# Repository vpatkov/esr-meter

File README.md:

# ESR meter

Yet another ESR meter. More precisely, it measures the impedance at 100 kHz in
assumption it's pure resistive. So this meter is not for laboratory
measurements, but for finding bad electrolytic capacitors (a typical fault in
aged electronics).

- The test signal is 100 kHz 50 mVpp 10 Ω sine wave
- Rechargeable from Micro-USB at 300 mA (Li-Po/Li-ion)
- Auto power-off after 3 minutes of inactivity

## Usage

To switch the meter on or off, press the button.

On startup, the meter performs a self-test. Keep the terminals open. During the
test, the meter turns on all the segments on the display, then shows an error
if any. Errors are:

- `E.F.LO`: low fuel (battery voltage < 3.3 V);
- `E.rEF`: something wrong with voltage references or ADC;
- `E.Prb`: something wrong with the test signal (or the terminals aren't open).

When the test is passed, the meter shows the current battery level in percents
as `F <level>`.

During normal operation the meter continuously shows the measured ESR in Ω,
or `-OL-` if it's more than 99.99 Ω.

To compensate test leads (set zero), short the leads and long press the button.
You can't compensate more than 2 Ω — find a better leads or connect capacitors
directly to the binding post. Note that inductance of wires matters at 100 kHz.
If the meter refuse to compensate, it shows `SHIt` (stands for "your leads are
shit").

## License

Unless otherwise noted, this work is licensed under Creative Commons Zero 1.0.

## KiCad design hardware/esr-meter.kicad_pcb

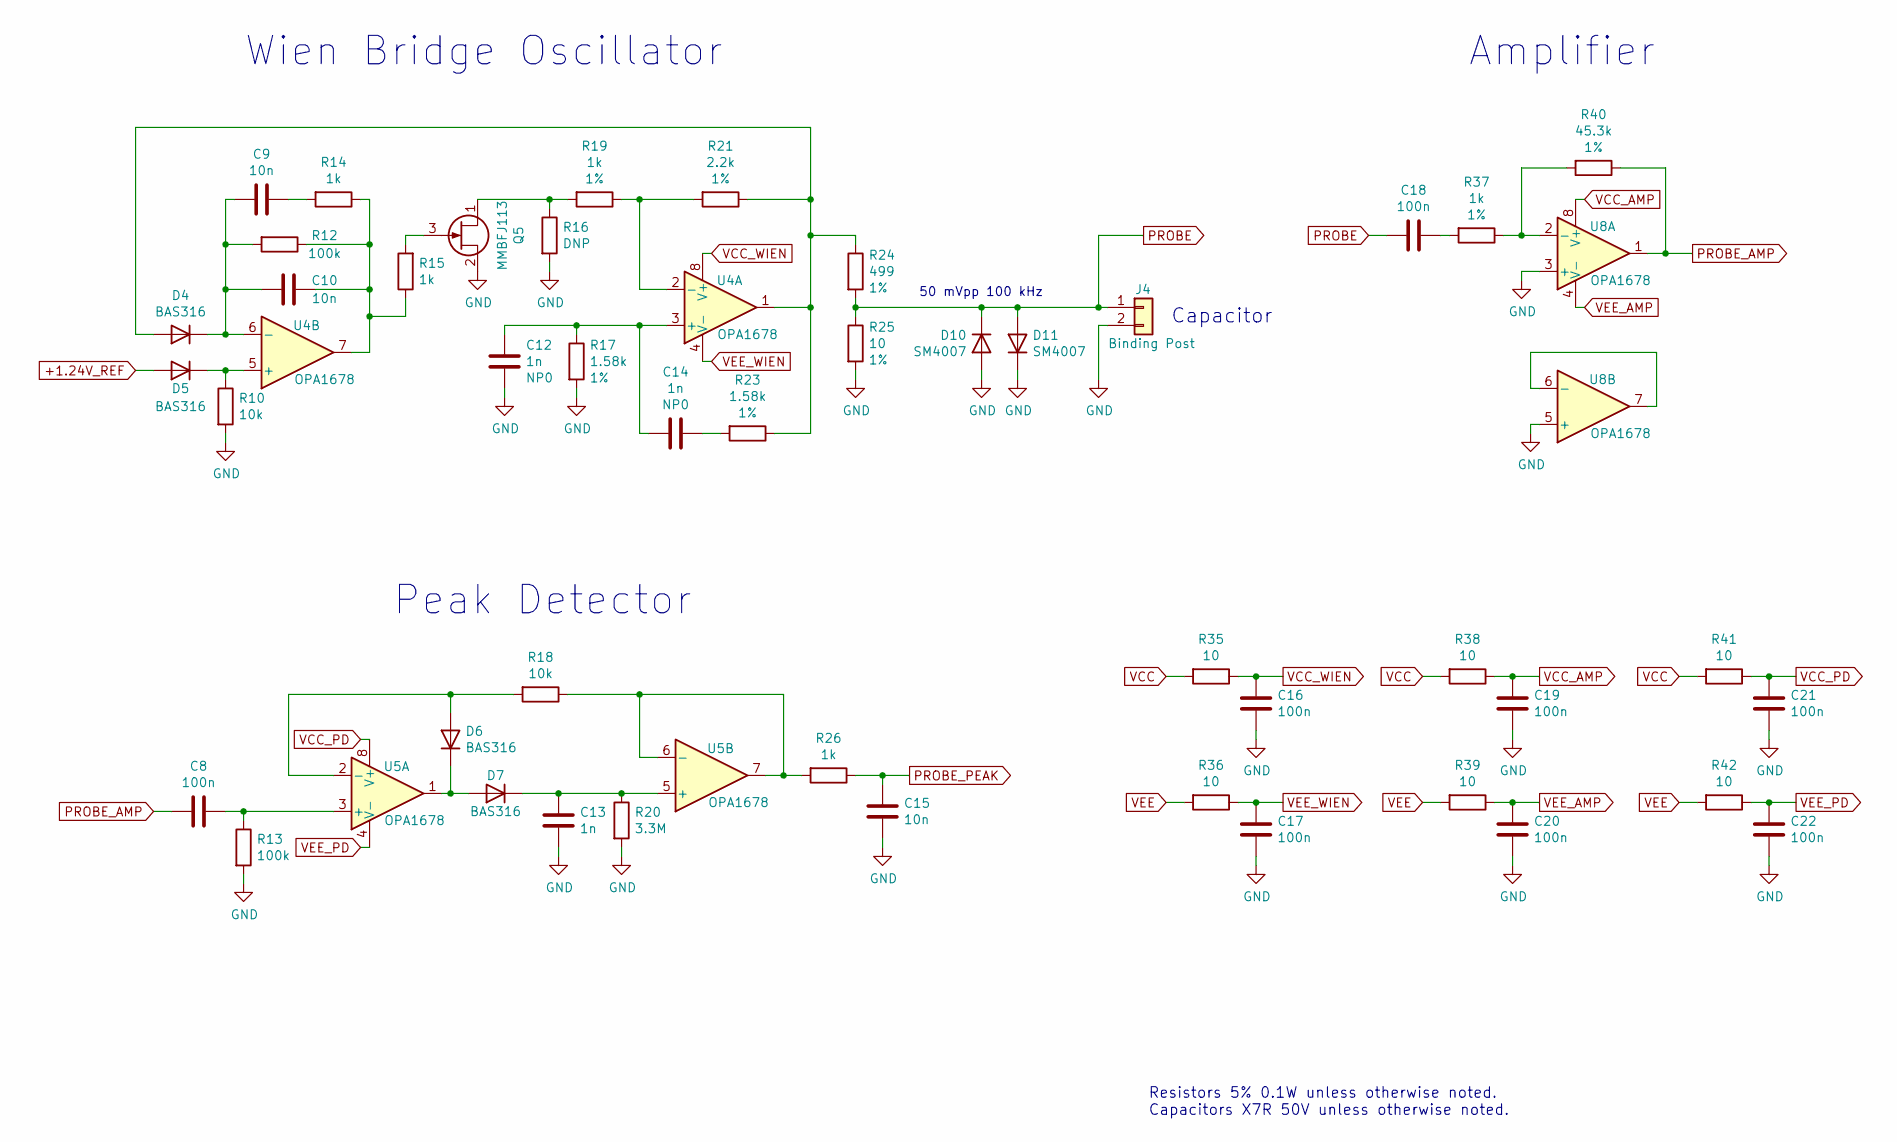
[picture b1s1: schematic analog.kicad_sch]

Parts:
C8, C16, C17, C18, C19, C20, C21, C22: 100n; C_0603_1608Metric
C9, C10, C15: 10n; C_0603_1608Metric
C12, C13, C14: 1n; C_0603_1608Metric
D4, D5, D6, D7: BAS316; D_SOD-323
D10, D11: SM4007; D_MELF
J4: Binding Post; BindingPost
Q5: MMBFJ113; SOT-23
R10, R18: 10k; R_0603_1608Metric
R12, R13: 100k; R_0603_1608Metric
R14, R15, R19, R26, R37: 1k; R_0603_1608Metric
R16: DNP; R_0603_1608Metric
R17, R23: 1.58k; R_0603_1608Metric
R20: 3.3M; R_0603_1608Metric
R21: 2.2k; R_0603_1608Metric
R24: 499; R_0805_2012Metric
R25: 10; R_0805_2012Metric
R35, R36, R38, R39, R41, R42: 10; R_0603_1608Metric
R40: 45.3k; R_0603_1608Metric
U4, U5, U8: OPA1678; SO-8_3.9x4.9mm_P1.27mm

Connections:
+1.24V_REF: D5.2 (A); also elsewhere on the board
GND: C12.2, C13.2, C15.2, C16.2, C17.2, C19.2, C20.2, C21.2, C22.2, D10.2 (A), D11.1 (K), J4.2, Q5.2 (S), R10.2, R13.2, R16.2, R17.2, R20.2, R25.2, U8.3 (+), U8.5 (+); also elsewhere on the board
unnamed: C9.1, R14.2
unnamed: C10.1, R12.1, R14.1, R15.1, U4.7
unnamed: C14.1, R23.2
unnamed: C18.1, R37.2
unnamed: D4.2 (A), R21.1, R23.1, R24.1, U4.1
unnamed: C9.2, C10.2, D4.1 (K), R12.2, U4.6 (-)
unnamed: D5.1 (K), R10.1, U4.5 (+)
unnamed: D6.2 (A), R18.2, U5.2 (-)
unnamed: D6.1 (K), D7.2 (A), U5.1
unnamed: C13.1, D7.1 (K), R20.1, U5.5 (+)
unnamed: Q5.1 (D), R16.1, R19.2
unnamed: Q5.3 (G), R15.2
unnamed: C12.1, C14.2, R17.1, U4.3 (+)
unnamed: R19.1, R21.2, U4.2 (-)
unnamed: C8.1, R13.1, U5.3 (+)
unnamed: R18.1, R26.2, U5.6 (-), U5.7
unnamed: R37.1, R40.2, U8.2 (-)
unnamed: U8.6 (-), U8.7
PROBE: C18.2, D10.1 (K), D11.2 (A), J4.1, R24.2, R25.1
PROBE_AMP: C8.2, R40.1, U8.1
PROBE_PEAK: C15.1, R26.1; also elsewhere on the board
VCC: R35.2, R38.2, R41.2; also elsewhere on the board
VCC_AMP: C19.1, R38.1, U8.8 (V+)
VCC_PD: C21.1, R41.1, U5.8 (V+)
VCC_WIEN: C16.1, R35.1, U4.8 (V+)
VEE: R36.2, R39.2, R42.2; also elsewhere on the board
VEE_AMP: C20.1, R39.1, U8.4 (V-)
VEE_PD: C22.1, R42.1, U5.4 (V-)
VEE_WIEN: C17.1, R36.1, U4.4 (V-)

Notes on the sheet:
50 mVpp 100 kHz
Amplifier
Peak Detector
Wien Bridge Oscillator
Resistors 5% 0.1W unless otherwise noted. Capacitors X7R 50V unless otherwise noted.
Capacitor

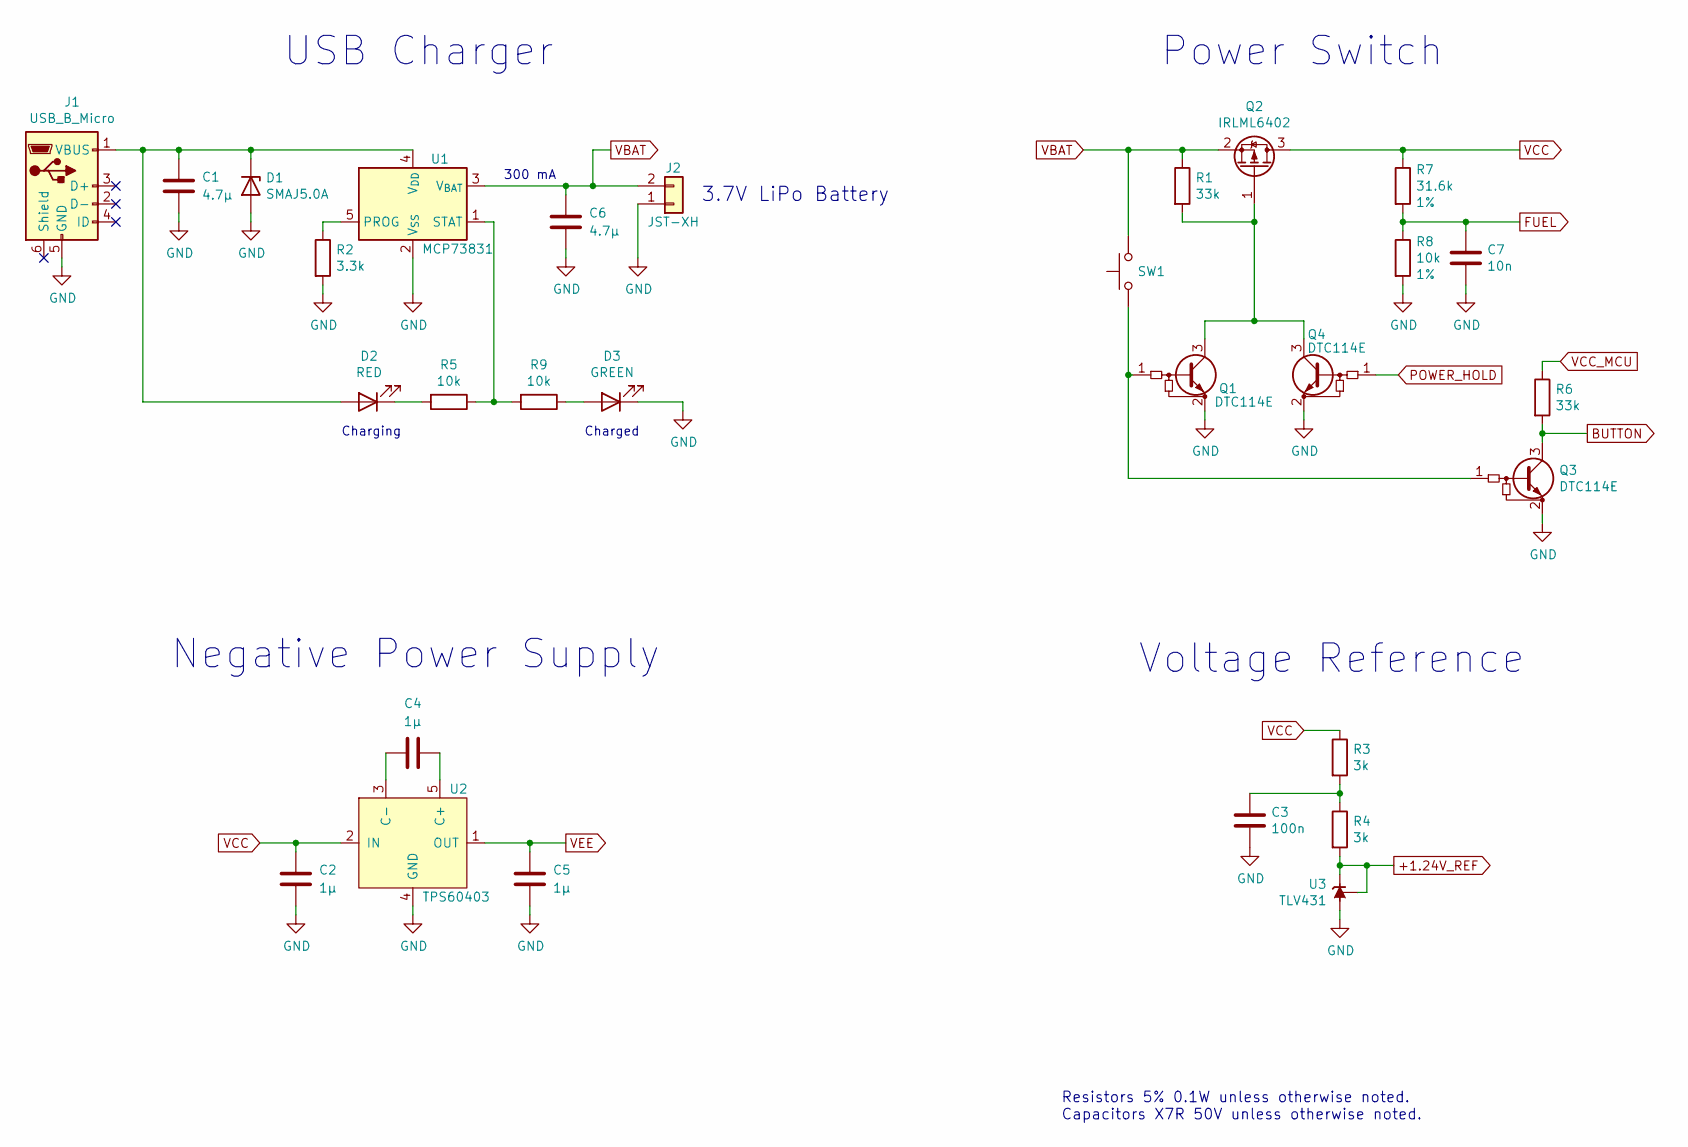
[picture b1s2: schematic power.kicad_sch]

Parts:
C1, C6: 4.7μ; C_1206_3216Metric
C2, C4, C5: 1μ; C_1206_3216Metric
C3: 100n; C_0603_1608Metric
C7: 10n; C_0603_1608Metric
D1: SMAJ5.0A; D_SMA
D2: RED; LED_1206_3216Metric
D3: GREEN; LED_1206_3216Metric
J1: USB_B_Micro; USB_Micro-B_Molex-105017-0001
J2: JST-XH; JST_XH_S2B-XH-A-1_1x02_P2.50mm_Horizontal
Q1, Q3, Q4: DTC114E; SOT-23
Q2: IRLML6402; SOT-23
R1, R6: 33k; R_0603_1608Metric
R2: 3.3k; R_0603_1608Metric
R3, R4: 3k; R_0603_1608Metric
R5, R8, R9: 10k; R_0603_1608Metric
R7: 31.6k; R_0603_1608Metric
SW1: SW_Push; SW_PUSH-12mm_Wuerth-430476085716
U1: MCP73831; SOT-23-5
U2: TPS60403; SOT-23-5
U3: TLV431; SOT-23

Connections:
+1.24V_REF: R4.2, U3.1 (K), U3.2 (REF); also elsewhere on the board
BUTTON: Q3.3 (C), R6.2; also elsewhere on the board
FUEL: C7.1, R7.2, R8.1; also elsewhere on the board
GND: C1.2, C2.2, C3.2, C5.2, C6.2, C7.2, D1.2 (A), D3.1 (K), J1.5 (GND), J2.1, Q1.2 (E), Q3.2 (E), Q4.2 (E), R2.2, R8.2, U1.2 (V_{SS}), U2.4 (GND), U3.3 (A); also elsewhere on the board
unnamed: C3.1, R3.2, R4.1
unnamed: C1.1, D1.1 (K), D2.2 (A), J1.1 (VBUS), U1.4 (V_{DD})
unnamed: D2.1 (K), R5.2
unnamed: D3.2 (A), R9.1
unnamed: Q1.1 (B), Q3.1 (B), SW1.1
unnamed: Q1.3 (C), Q2.1 (G), Q4.3 (C), R1.2
unnamed: R2.1, U1.5 (PROG)
unnamed: R5.1, R9.2, U1.1 (STAT)
unnamed: C4.1, U2.5 (C+)
unnamed: C4.2, U2.3 (C-)
POWER_HOLD: Q4.1 (B); also elsewhere on the board
VBAT: C6.1, J2.2, Q2.2 (S), R1.1, SW1.2, U1.3 (V_{BAT}); also elsewhere on the board
VCC: C2.1, Q2.3 (D), R3.1, R7.1, U2.2 (IN); also elsewhere on the board
VCC_MCU: R6.1; also elsewhere on the board
VEE: C5.1, U2.1 (OUT); also elsewhere on the board

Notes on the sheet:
USB Charger
Charging
3.7V LiPo Battery
Resistors 5% 0.1W unless otherwise noted. Capacitors X7R 50V unless otherwise noted.
Voltage Reference
Power Switch
300 mA
Charged
Negative Power Supply

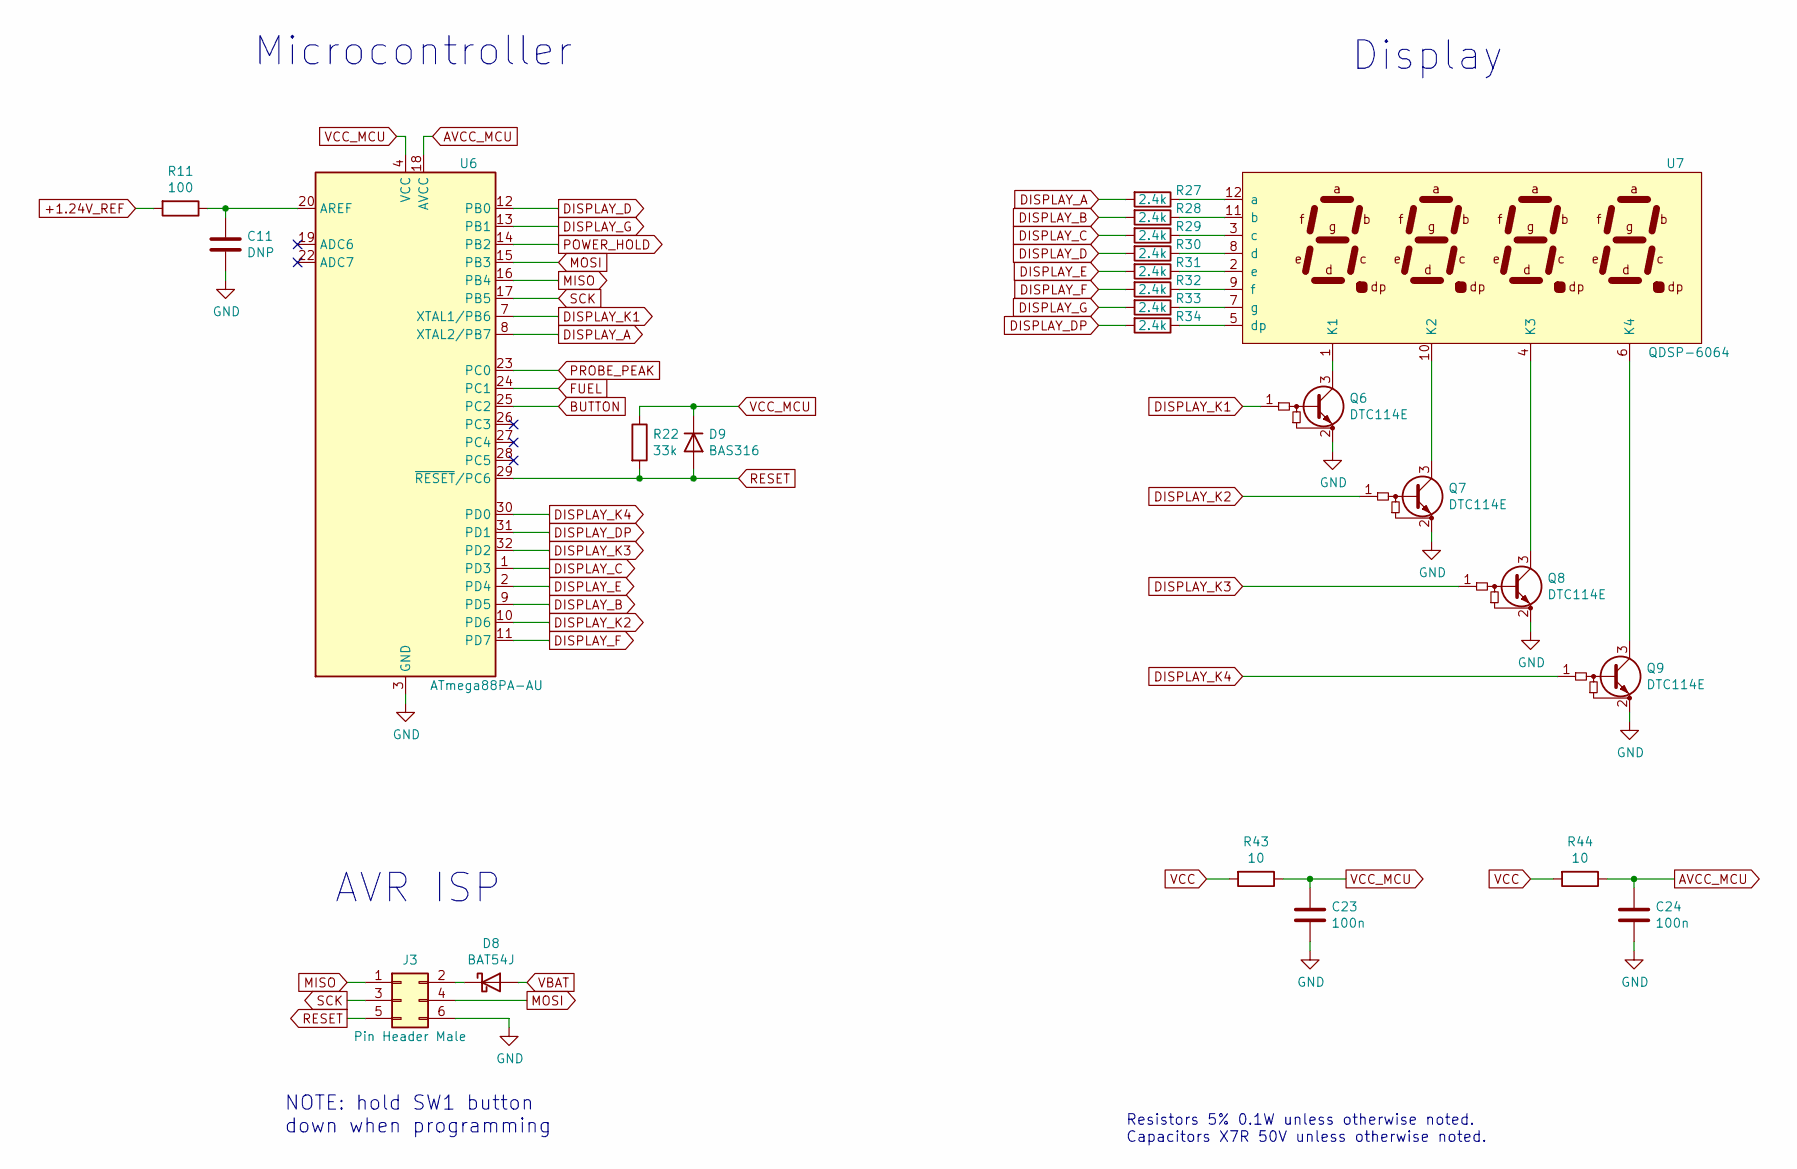
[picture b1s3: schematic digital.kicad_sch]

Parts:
C11: DNP; C_0603_1608Metric
C23, C24: 100n; C_0603_1608Metric
D8: BAT54J; D_SOD-323F
D9: BAS316; D_SOD-323
J3: Pin Header Male; PinHeader_2x03_P2.54mm_Vertical
Q6, Q7, Q8, Q9: DTC114E; SOT-23
R11: 100; R_0603_1608Metric
R22: 33k; R_0603_1608Metric
R27, R28, R29, R30, R31, R32, R33, R34: 2.4k; R_0603_1608Metric
R43, R44: 10; R_0603_1608Metric
U6: ATmega88PA-AU; TQFP-32_7x7mm_P0.8mm
U7: QDSP-6064; DIP-12_W7.62mm

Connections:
+1.24V_REF: R11.2; also elsewhere on the board
AVCC_MCU: C24.1, R44.1, U6.18 (AVCC)
BUTTON: U6.25 (PC2); also elsewhere on the board
DISPLAY_A: R27.2, U6.8 (XTAL2/PB7)
DISPLAY_B: R28.2, U6.9 (PD5)
DISPLAY_C: R29.2, U6.1 (PD3)
DISPLAY_D: R30.2, U6.12 (PB0)
DISPLAY_DP: R34.2, U6.31 (PD1)
DISPLAY_E: R31.2, U6.2 (PD4)
DISPLAY_F: R32.2, U6.11 (PD7)
DISPLAY_G: R33.2, U6.13 (PB1)
DISPLAY_K1: Q6.1 (B), U6.7 (XTAL1/PB6)
DISPLAY_K2: Q7.1 (B), U6.10 (PD6)
DISPLAY_K3: Q8.1 (B), U6.32 (PD2)
DISPLAY_K4: Q9.1 (B), U6.30 (PD0)
FUEL: U6.24 (PC1); also elsewhere on the board
GND: C11.2, C23.2, C24.2, J3.6, Q6.2 (E), Q7.2 (E), Q8.2 (E), Q9.2 (E), U6.3 (GND), U6.5 (GND), U6.21 (GND); also elsewhere on the board
MISO: J3.1, U6.16 (PB4)
MOSI: J3.4, U6.15 (PB3)
unnamed: D8.1 (K), J3.2
unnamed: Q6.3 (C), U7.1 (K1)
unnamed: Q7.3 (C), U7.10 (K2)
unnamed: Q8.3 (C), U7.4 (K3)
unnamed: Q9.3 (C), U7.6 (K4)
unnamed: C11.1, R11.1, U6.20 (AREF)
unnamed: R27.1, U7.12 (a)
unnamed: R28.1, U7.11 (b)
unnamed: R29.1, U7.3 (c)
unnamed: R30.1, U7.8 (d)
unnamed: R34.1, U7.5 (dp)
unnamed: R31.1, U7.2 (e)
unnamed: R32.1, U7.9 (f)
unnamed: R33.1, U7.7 (g)
POWER_HOLD: U6.14 (PB2); also elsewhere on the board
PROBE_PEAK: U6.23 (PC0); also elsewhere on the board
RESET: D9.2 (A), J3.5, R22.2, U6.29 (~RESET/PC6)
SCK: J3.3, U6.17 (PB5)
VBAT: D8.2 (A); also elsewhere on the board
VCC: R43.2, R44.2; also elsewhere on the board
VCC_MCU: C23.1, D9.1 (K), R22.1, R43.1, U6.4 (VCC), U6.6 (VCC); also elsewhere on the board

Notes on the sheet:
Display
Resistors 5% 0.1W unless otherwise noted. Capacitors X7R 50V unless otherwise noted.
Microcontroller
NOTE: hold SW1 button down when programming
AVR ISP

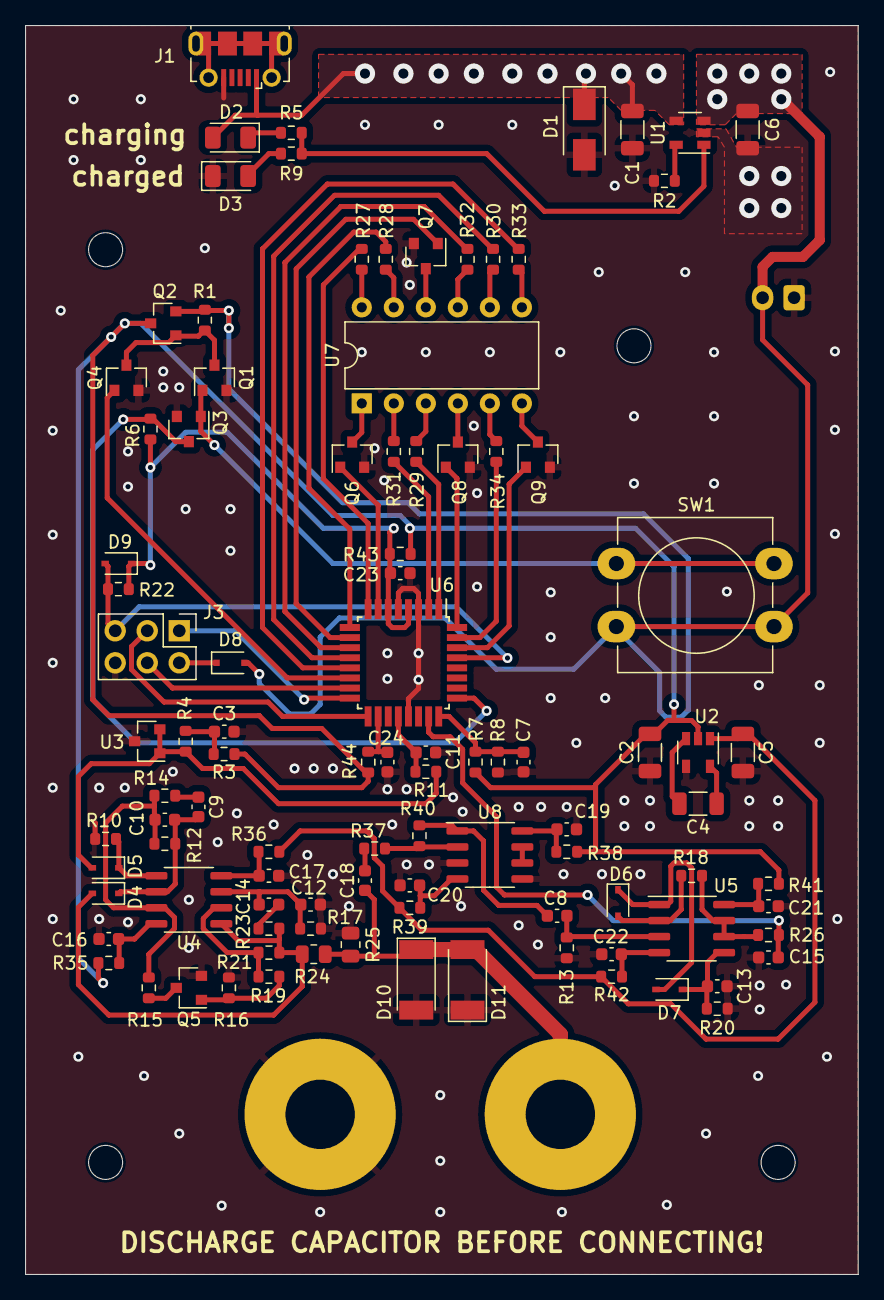
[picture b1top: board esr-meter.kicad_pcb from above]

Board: 2 copper layers, 66.0 x 99.1 mm, 101 parts (1 on the bottom side), 77 nets.

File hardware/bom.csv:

"#","Reference","Qty","Value","Footprint","DNP","Note"
"1","C1, C6","2","4.7μ","Capacitor_SMD:C_1206_3216Metric","",""
"2","C2, C4, C5","3","1μ","Capacitor_SMD:C_1206_3216Metric","",""
"3","C3, C8, C16, C17, C18, C19, C20, C21, C22, C23, C24","11","100n","Capacitor_SMD:C_0603_1608Metric","",""
"4","C7, C9, C10, C15","4","10n","Capacitor_SMD:C_0603_1608Metric","",""
"5","C11","1","","Capacitor_SMD:C_0603_1608Metric","DNP",""
"6","C12, C14","2","1n","Capacitor_SMD:C_0603_1608Metric","","NP0"
"7","C13","1","1n","Capacitor_SMD:C_0603_1608Metric","",""
"8","D1","1","SMAJ5.0A","Diode_SMD:D_SMA","",""
"9","D2","1","RED","LED_SMD:LED_1206_3216Metric","",""
"10","D3","1","GREEN","LED_SMD:LED_1206_3216Metric","",""
"11","D4, D5, D6, D7, D9","5","BAS316","Diode_SMD:D_SOD-323","",""
"12","D8","1","BAT54J","Diode_SMD:D_SOD-323F","",""
"13","D10, D11","2","SM4007","Diode_SMD:D_MELF","",""
"14","J1","1","USB_B_Micro","Connector_USB:USB_Micro-B_Molex-105017-0001","",""
"15","J2","1","JST-XH","Connector_JST:JST_XH_S2B-XH-A-1_1x02_P2.50mm_Horizontal","",""
"16","J3","1","Pin Header Male","Connector_PinHeader_2.54mm:PinHeader_2x03_P2.54mm_Vertical","",""
"17","J4","1","Binding Post","esr-meter:BindingPost","",""
"18","Q1, Q3, Q4, Q6, Q7, Q8, Q9","7","DTC114E","Package_TO_SOT_SMD:SOT-23","",""
"19","Q2","1","IRLML6402","Package_TO_SOT_SMD:SOT-23","",""
"20","Q5","1","MMBFJ113","Package_TO_SOT_SMD:SOT-23","",""
"21","R1, R6, R22","3","33k","Resistor_SMD:R_0603_1608Metric","",""
"22","R2","1","3.3k","Resistor_SMD:R_0603_1608Metric","",""
"23","R3, R4","2","3k","Resistor_SMD:R_0603_1608Metric","",""
"24","R5, R9, R10, R18","4","10k","Resistor_SMD:R_0603_1608Metric","",""
"25","R7","1","31.6k","Resistor_SMD:R_0603_1608Metric","","1%"
"26","R8","1","10k","Resistor_SMD:R_0603_1608Metric","","1%"
"27","R11","1","100","Resistor_SMD:R_0603_1608Metric","",""
"28","R12, R13","2","100k","Resistor_SMD:R_0603_1608Metric","",""
"29","R14, R15, R26","3","1k","Resistor_SMD:R_0603_1608Metric","",""
"30","R16","1","","Resistor_SMD:R_0603_1608Metric","DNP",""
"31","R17, R23","2","1.58k","Resistor_SMD:R_0603_1608Metric","","1%"
"32","R19, R37","2","1k","Resistor_SMD:R_0603_1608Metric","","1%"
"33","R20","1","3.3M","Resistor_SMD:R_0603_1608Metric","",""
"34","R21","1","2.2k","Resistor_SMD:R_0603_1608Metric","","1%"
"35","R24","1","499","Resistor_SMD:R_0805_2012Metric","","1%"
"36","R25","1","10","Resistor_SMD:R_0805_2012Metric","","1%"
"37","R27, R28, R29, R30, R31, R32, R33, R34","8","2.4k","Resistor_SMD:R_0603_1608Metric","",""
"38","R35, R36, R38, R39, R41, R42, R43, R44","8","10","Resistor_SMD:R_0603_1608Metric","",""
"39","R40","1","45.3k","Resistor_SMD:R_0603_1608Metric","","1%"
"40","SW1","1","SW_Push","Button_Switch_THT:SW_PUSH-12mm_Wuerth-430476085716","",""
"41","U1","1","MCP73831","Package_TO_SOT_SMD:SOT-23-5","",""
"42","U2","1","TPS60403","Package_TO_SOT_SMD:SOT-23-5","",""
"43","U3","1","TLV431","Package_TO_SOT_SMD:SOT-23","",""
"44","U4, U5, U8","3","OPA1678","Package_SO:SO-8_3.9x4.9mm_P1.27mm","",""
"45","U6","1","ATmega88PA-AU","Package_QFP:TQFP-32_7x7mm_P0.8mm","",""
"46","U7","1","QDSP-6064","Package_DIP:DIP-12_W7.62mm","",""

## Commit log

2022-02-13 Auto power-off
2023-05-18 Update to KiCad 7 and some minor changes
2023-05-20 Split A2 circuit into A4 pages
2023-05-24 Increase ADC resolution
2023-05-24 Ensure safe GPIO PORT/DDR write order
2023-05-26 Change R11 to 100 ohm
2023-06-21 README cosmetic changes
2023-06-24 Update GPIO module
2023-06-25 Added BOM and the assembly diagram
